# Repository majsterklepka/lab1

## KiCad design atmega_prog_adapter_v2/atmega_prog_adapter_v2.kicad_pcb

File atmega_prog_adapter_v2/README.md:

# ATmega adapter
electronics workshop

Hi!

Now here I present a project of ATmega programmer adapter. For what is them? For You! Schematic is very simple, just one ZIF socket, one Kanda socket and a few discrete elements. Project was made with use of KiCad, and graphics are prepare with use of Inkscape. Below I present a Schematic Sheet:

This adapter is used for flashing following devices:

- ATmega48A
- ATmega48PA
- ATmega88A
- ATmega88PA
- ATmega168A
- ATmega168PA
- ATmega328
- ATmega328P

Of course this adapter needs to work a programmer, for example: USBasp or ArduinoISP. Below is shown 3D view of PCB Layout(without showing elements):

and here, is shown a 2d view of PCB Layout:

These all programmers, their projects are published in my repository [here](https://github.com/majsterklepka/avr-programmers.git "MajsterKlepka AVR-PROGRAMMERS Repo")

Have a fun and do not wake up the neighbors during night fun, because this occupation is very addictive and exciting! Feel free and share this project with friends!

_MSc. Paweł Sobótka (SQ7EQE)_

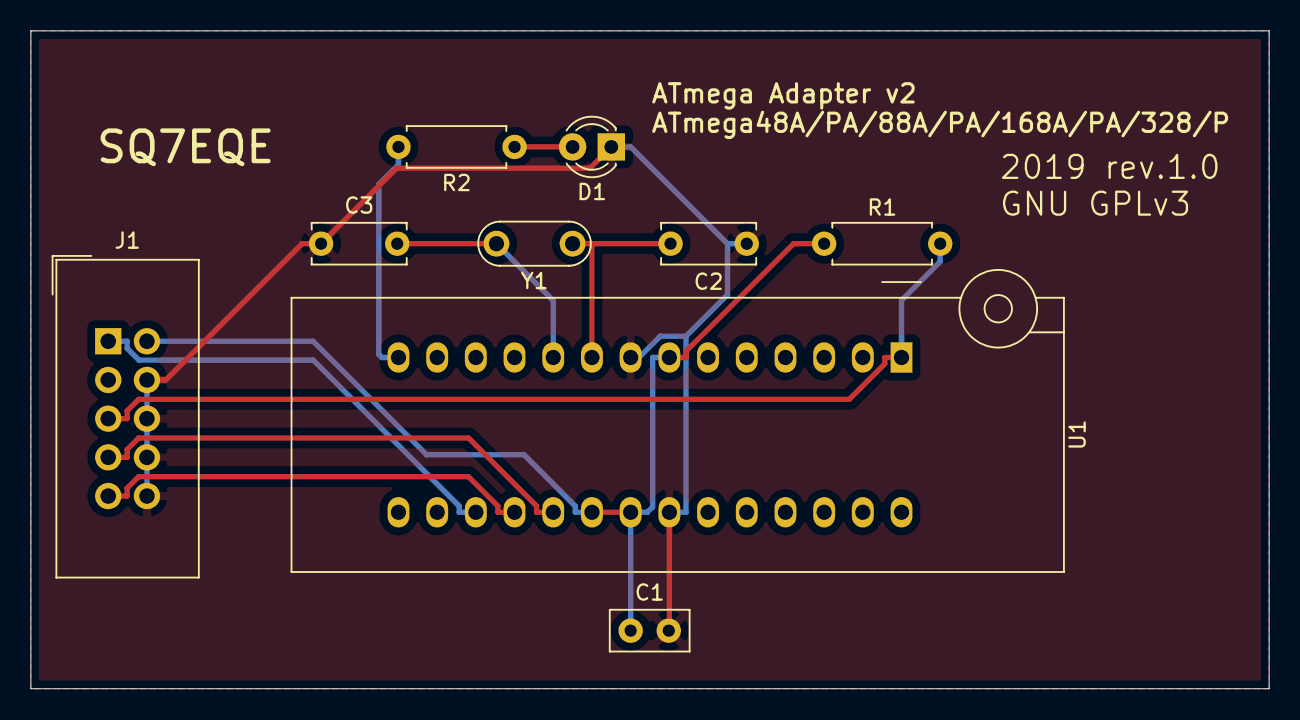
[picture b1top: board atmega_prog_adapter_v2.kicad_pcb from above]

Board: 2 copper layers, 81.3 x 43.2 mm, 9 parts (0 on the bottom side), 10 nets.

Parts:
C1: 0.1u; C_Disc_D5.0mm_W2.5mm_P2.50mm
C2, C3: 22p; C_Disc_D6.0mm_W2.5mm_P5.00mm
D1: YELLOW; LED_D3.0mm
J1: AVR-ISP-10; IDC-Header_2x05_P2.54mm_Vertical
R1: 10k; R_Axial_DIN0207_L6.3mm_D2.5mm_P7.62mm_Horizontal
R2: 470; R_Axial_DIN0207_L6.3mm_D2.5mm_P7.62mm_Horizontal
U1: ATmega48A/PA/88A/PA/168A/PA/328/P; DIP_Socket-28_W6.9_W7.62_W10.16_W12.7_W13.5_3M_228-4817-00-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
Y1: XTAL; Resonator-2Pin_W7.0mm_H2.5mm

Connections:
/MISO: J1.9, U1.18
/MOSI: J1.1, U1.17
/RESET: J1.5, R1.2, U1.1
/SCK: J1.7, U1.19
/XTAL1: C2.2, U1.9, Y1.1
/XTAL2: C3.2, U1.10, Y1.2
GND: C1.2, C2.1, C3.1, D1.1, J1.4, J1.6, J1.8, J1.10, U1.8, U1.22
unnamed: C1.1, J1.2, R1.1, U1.7, U1.20, U1.21
unnamed: D1.2, R2.1
unnamed: R2.2, U1.14

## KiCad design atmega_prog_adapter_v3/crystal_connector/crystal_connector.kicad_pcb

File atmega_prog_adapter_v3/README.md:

# ATmega adapter v3
electronics workshop

Hi, My Dear Friends! 

Here we have the next version of my ATmega adapter project. This project has excluded from main circuit quartz crystal with capacitors, which is a separate module, a sub-project. Of course, this project was created using KiCad and, like the others, is licensed under Free License (GNU GPLv3). The root directory contains Gerber files, as does the sub-project directory. Today I do not place any graphics, all the necessary information is in the documentation.

Feel free and share this project with your friends!

_MSc. Paweł Sobótka (SQ7EQE)_

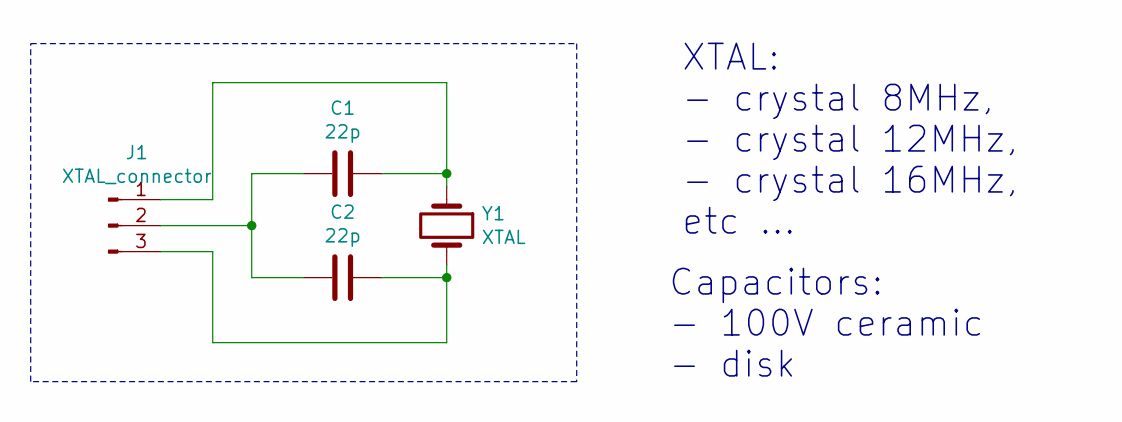
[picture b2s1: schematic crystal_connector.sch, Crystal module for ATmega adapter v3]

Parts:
C1, C2: 22p; C_Disc_D4.3mm_W1.9mm_P5.00mm
J1: XTAL_connector; PinHeader_1x03_P2.54mm_Horizontal
Y1: XTAL; Crystal_HC50_Vertical

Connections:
unnamed: C1.1, J1.1, Y1.1
unnamed: C1.2, C2.2, J1.2
unnamed: C2.1, J1.3, Y1.2

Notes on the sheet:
XTAL: - crystal 8MHz, - crystal 12MHz, - crystal 16MHz, etc ...
Capacitors: - 100V ceramic - disk

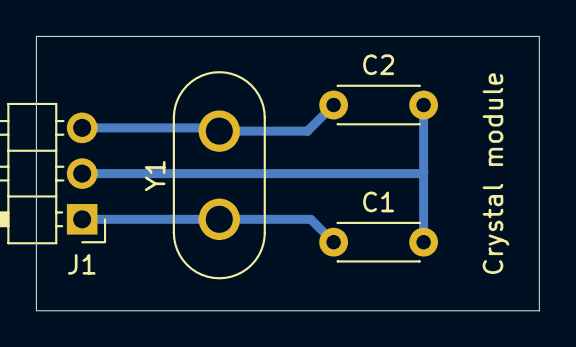
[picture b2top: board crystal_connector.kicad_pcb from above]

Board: 2 copper layers, 27.9 x 15.2 mm, 4 parts (0 on the bottom side), 3 nets.

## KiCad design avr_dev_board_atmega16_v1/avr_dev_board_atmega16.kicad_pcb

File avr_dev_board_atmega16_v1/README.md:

# AVR Atmega16 Dev Board v1
electronics workshop

Hi! Here I have a proposal for you! A Development AVR Board with Atmega16A microcontrollers. This version haven't built-in linear voltage regulator, here you see a 3D PCB layout view:

Schematic sheet is present below and of course, as KiCad project into this folder:

And, as you see, PCB layout project:

Of course, you can look inside drawings/ folder, you see there a PDF documents.

Have a fun with that project!

_MSc. Paweł Sobótka (SQ7EQE)_

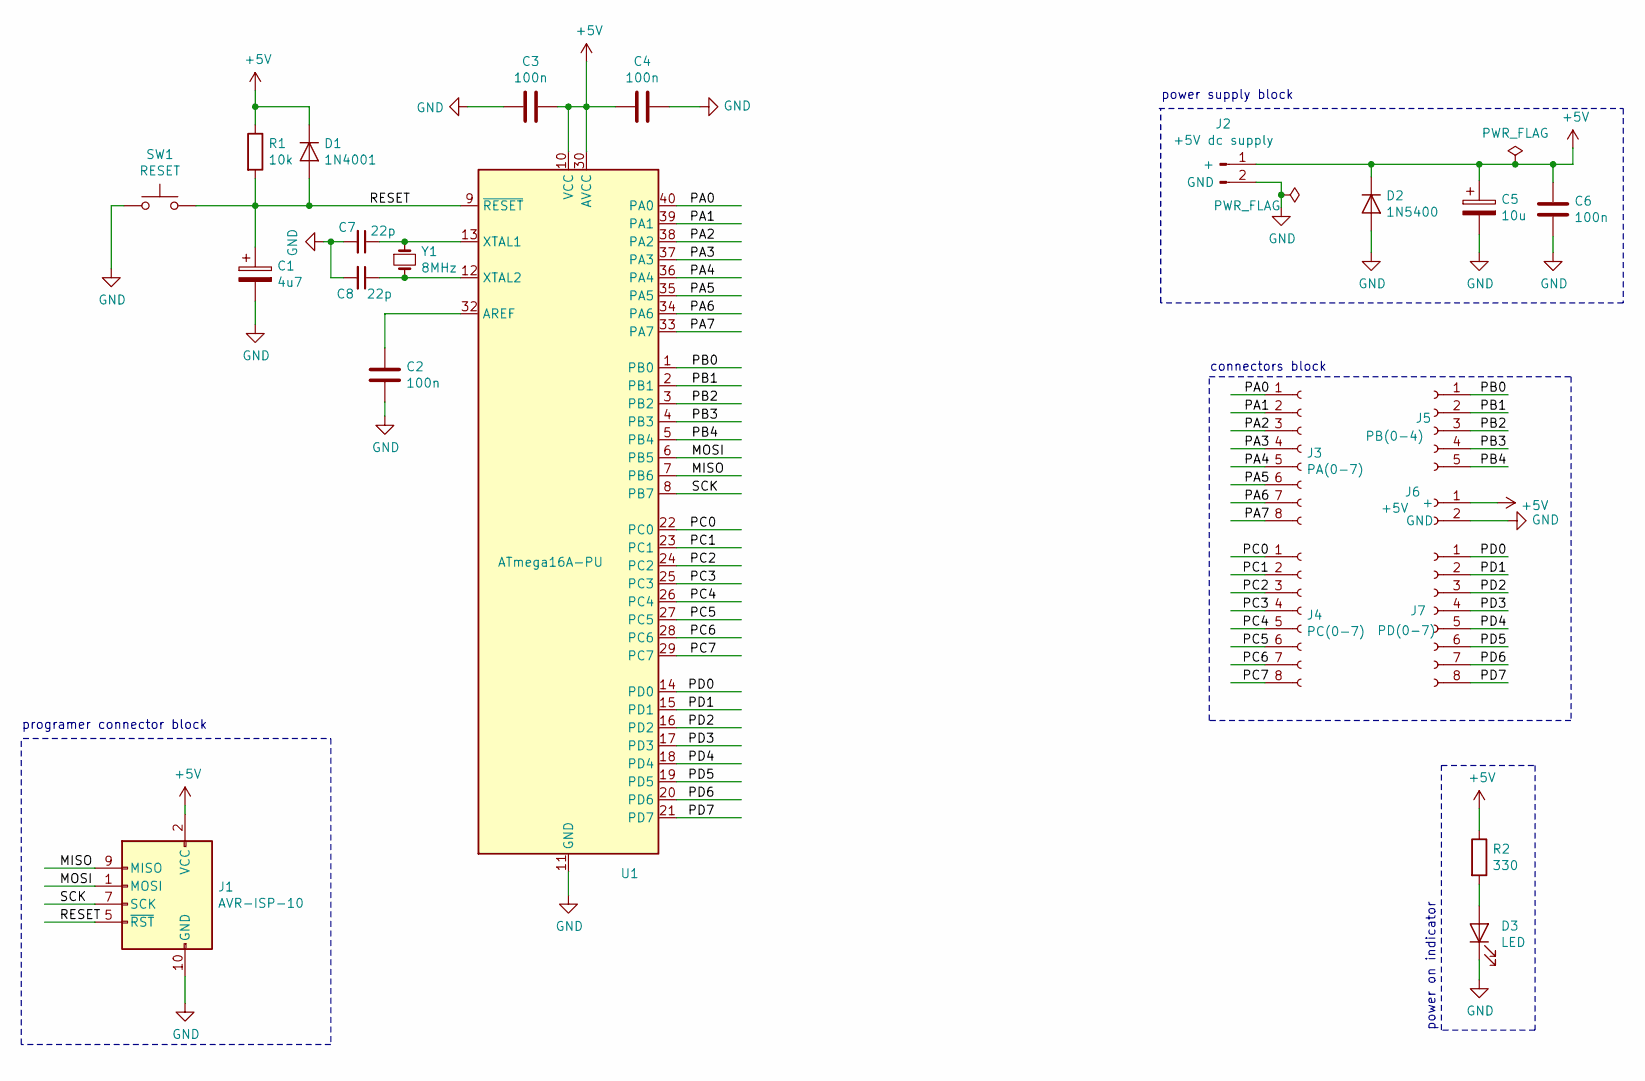
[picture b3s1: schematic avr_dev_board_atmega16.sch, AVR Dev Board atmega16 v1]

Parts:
C1: 4u7; CP_Radial_D5.0mm_P2.50mm
C2, C3, C4, C6: 100n; C_Disc_D4.3mm_W1.9mm_P5.00mm
C5: 10u; CP_Radial_D6.3mm_P2.50mm
C7, C8: 22p; C_Disc_D4.7mm_W2.5mm_P5.00mm
D1: 1N4001; D_DO-41_SOD81_P10.16mm_Horizontal
D2: 1N5400; D_DO-201AD_P15.24mm_Horizontal
D3: LED; LED_D3.0mm
J1: AVR-ISP-10; IDC-Header_2x05_P2.54mm_Vertical
J2: +5V dc supply; PinHeader_1x02_P2.54mm_Vertical_PWR
J3: PA(0-7); PinSocket_1x08_P2.54mm_Vertical_PA
J4: PC(0-7); PinSocket_1x08_P2.54mm_Vertical_PC
J5: PB(0-4); PinSocket_1x05_P2.54mm_Vertical_PB
J6: +5V; PinSocket_1x02_P2.54mm_Vertical_PWR
J7: PD(0-7); PinSocket_1x08_P2.54mm_Vertical_PD
R1: 10k; R_Axial_DIN0309_L9.0mm_D3.2mm_P2.54mm_Vertical
R2: 330; R_Axial_DIN0309_L9.0mm_D3.2mm_P2.54mm_Vertical
SW1: RESET; SW_PUSH_6mm_H5mm
U1: ATmega16A-PU; DIP-40_W15.24mm
Y1: 8MHz; Resonator-2Pin_W6.0mm_H3.0mm

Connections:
+5V: C3.1, C4.2, C5.1, C6.1, D1.1 (K), D2.1 (K), J1.2 (VCC), J2.1 (+), J6.1 (+), R1.1, R2.1, U1.10 (VCC), U1.30 (AVCC)
/MISO: J1.9 (MISO), U1.7 (PB6)
/MOSI: J1.1 (MOSI), U1.6 (PB5)
/PA0: J3.1, U1.40 (PA0)
/PA1: J3.2, U1.39 (PA1)
/PA2: J3.3, U1.38 (PA2)
/PA3: J3.4, U1.37 (PA3)
/PA4: J3.5, U1.36 (PA4)
/PA5: J3.6, U1.35 (PA5)
/PA6: J3.7, U1.34 (PA6)
/PA7: J3.8, U1.33 (PA7)
/PB0: J5.1, U1.1 (PB0)
/PB1: J5.2, U1.2 (PB1)
/PB2: J5.3, U1.3 (PB2)
/PB3: J5.4, U1.4 (PB3)
/PB4: J5.5, U1.5 (PB4)
/PC0: J4.1, U1.22 (PC0)
/PC1: J4.2, U1.23 (PC1)
/PC2: J4.3, U1.24 (PC2)
/PC3: J4.4, U1.25 (PC3)
/PC4: J4.5, U1.26 (PC4)
/PC5: J4.6, U1.27 (PC5)
/PC6: J4.7, U1.28 (PC6)
/PC7: J4.8, U1.29 (PC7)
/PD0: J7.1, U1.14 (PD0)
/PD1: J7.2, U1.15 (PD1)
/PD2: J7.3, U1.16 (PD2)
/PD3: J7.4, U1.17 (PD3)
/PD4: J7.5, U1.18 (PD4)
/PD5: J7.6, U1.19 (PD5)
/PD6: J7.7, U1.20 (PD6)
/PD7: J7.8, U1.21 (PD7)
/RESET: C1.1, D1.2 (A), J1.5 (~RST), R1.2, SW1.2, U1.9 (~RESET)
/SCK: J1.7 (SCK), U1.8 (PB7)
GND: C1.2, C2.2, C3.2, C4.1, C5.2, C6.2, C7.2, C8.2, D2.2 (A), D3.1 (K), J1.4 (GND), J1.6 (GND), J1.8 (GND), J1.10 (GND), J2.2 (GND), J6.2 (GND), SW1.1, U1.11 (GND), U1.31 (GND)
unnamed: C2.1, U1.32 (AREF)
unnamed: C7.1, U1.13 (XTAL1), Y1.1
unnamed: C8.1, U1.12 (XTAL2), Y1.2
unnamed: D3.2 (A), R2.2

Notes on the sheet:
power supply block
connectors block
programer connector block
power on indicator

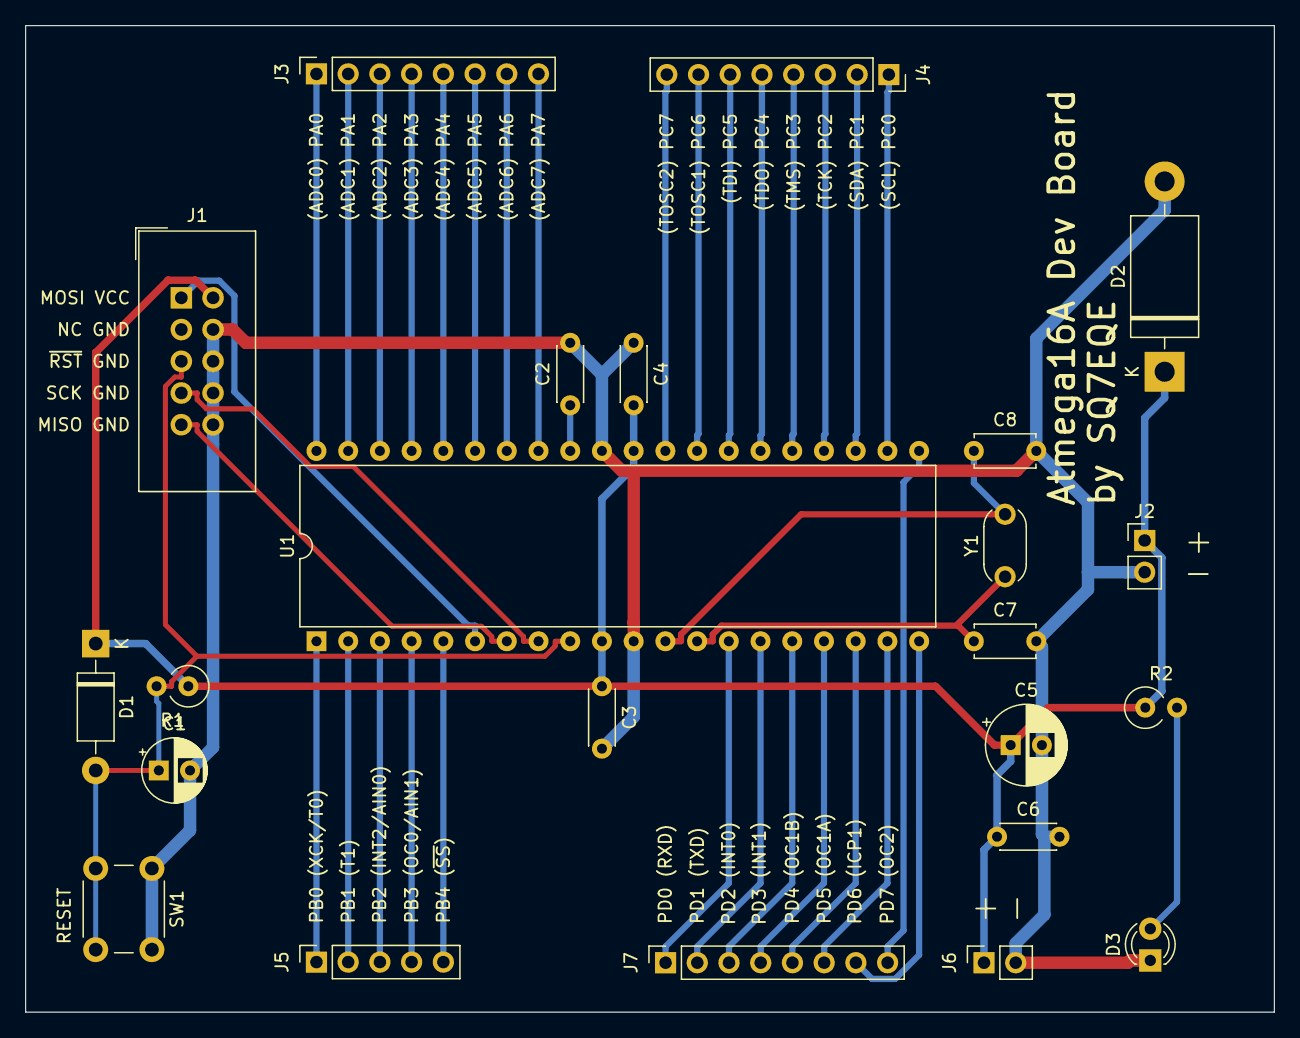
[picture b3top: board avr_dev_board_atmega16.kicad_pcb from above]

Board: 2 copper layers, 100.0 x 79.0 mm, 23 parts (0 on the bottom side), 39 nets.

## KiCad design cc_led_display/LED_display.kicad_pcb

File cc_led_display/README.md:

# Experimental CC LED Display
electronics workshop

Now, I present a simple, no! The simplest project, one difficulty is that this project requires double side PCB. You can use them for Arduino Projects, AVR Projects(for example with my Dev Board) and for what you only wish! Here is a schematic diagram:

Here You have a view of PCB in 3D, generated with Kicad 3DView:

What you need to make this project? Here is a list

- 8 x 1k resistor 0.125W
- 1 x OPD-S5621G-BW LED display with common cathode
- 1 x PCB
- solder, soldering iron, flux, side cutters, tweezers ...

I will be forgotten! I make a PCB project too! Here you have one:

Have fun! Feel free and share this project with friends! The project has two licenses: GNU GPLv3 and GNU FDL-1.3. You can use it as you wish, but please, remember about The Author!

_MSc. Paweł Sobótka (SQ7EQE)_

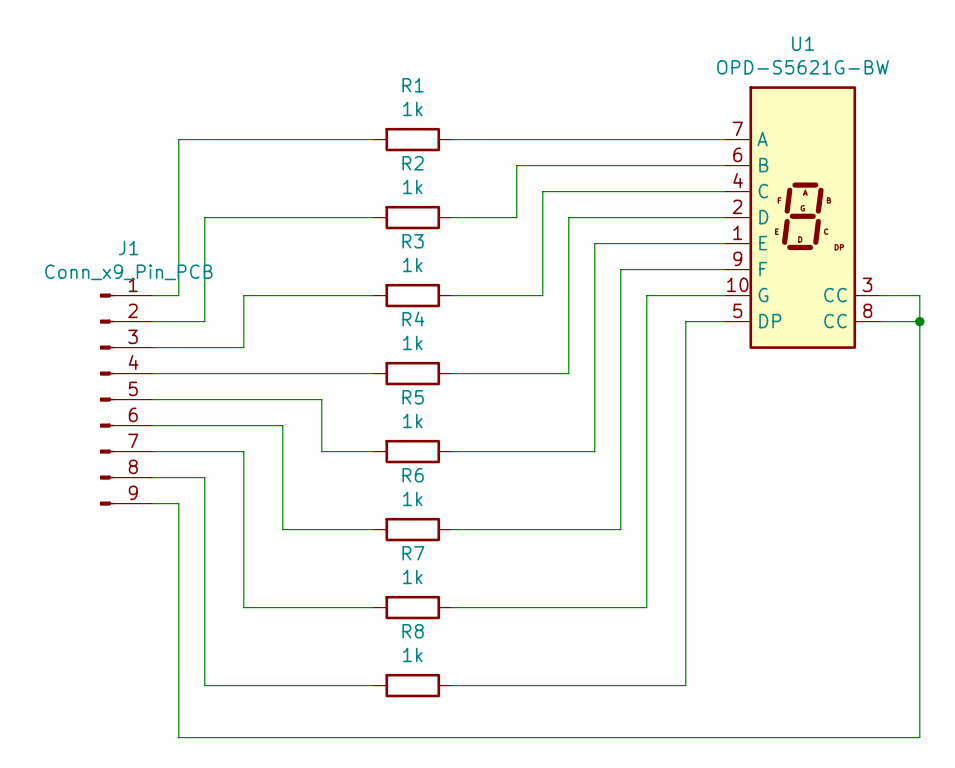
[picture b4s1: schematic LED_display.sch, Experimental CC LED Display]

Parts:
J1: Conn_x9_Pin_PCB; con_pingold_9_P2.54
R1, R2, R3, R4, R5, R6, R7, R8: 1k; R_Axial_DIN0204_L3.6mm_D1.6mm_P7.62mm_Horizontal
U1: OPD-S5621G-BW; led_0.56

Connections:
unnamed: J1.1, R1.2
unnamed: J1.2, R2.2
unnamed: J1.3, R3.2
unnamed: J1.4, R4.2
unnamed: J1.5, R5.2
unnamed: J1.6, R6.2
unnamed: J1.7, R7.2
unnamed: J1.8, R8.2
unnamed: J1.9, U1.3 (CC), U1.8 (CC)
unnamed: R1.1, U1.7 (A)
unnamed: R2.1, U1.6 (B)
unnamed: R3.1, U1.4 (C)
unnamed: R4.1, U1.2 (D)
unnamed: R5.1, U1.1 (E)
unnamed: R6.1, U1.9 (F)
unnamed: R7.1, U1.10 (G)
unnamed: R8.1, U1.5 (DP)

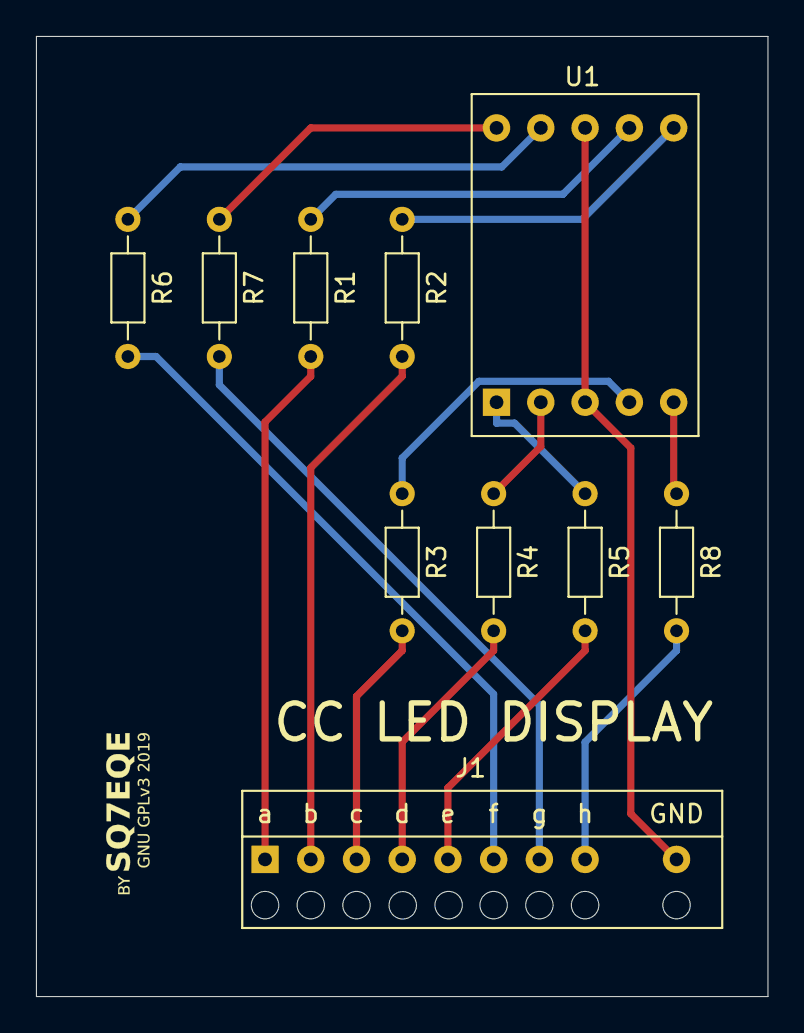
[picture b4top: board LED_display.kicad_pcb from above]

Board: 2 copper layers, 40.6 x 53.3 mm, 10 parts (0 on the bottom side), 17 nets.

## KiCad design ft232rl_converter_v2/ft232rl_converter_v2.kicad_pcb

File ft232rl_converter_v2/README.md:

# FT232RL USB-TTL-UART converter ver. 2.0

Hi, My Dear Friends!

Today, I have to present for You New Project. This is a simple use of the Manufacturer Application Note of FT232RL chip. Here you have a 3D View of PCB layout:

At the root tree of the project folder, you can find a file named BOM with various extensions. This is a list used in the project materials. Of course, I remember about ship to you a schematic diagram, here we have one:

Especially for You, I have design the PCB layout, here you have one:

In the folder named plot/ I have placed a generated Gerber files for the project.

And like usual, this project is licensed under GNU GPLv3 license and FDL-1.3 license. Feel free! Share this project with friends and don't forget about author ye the way!

See You Later & with my pleasure for You!

_MSc. Paweł Sobótka (SQ7EQE)_

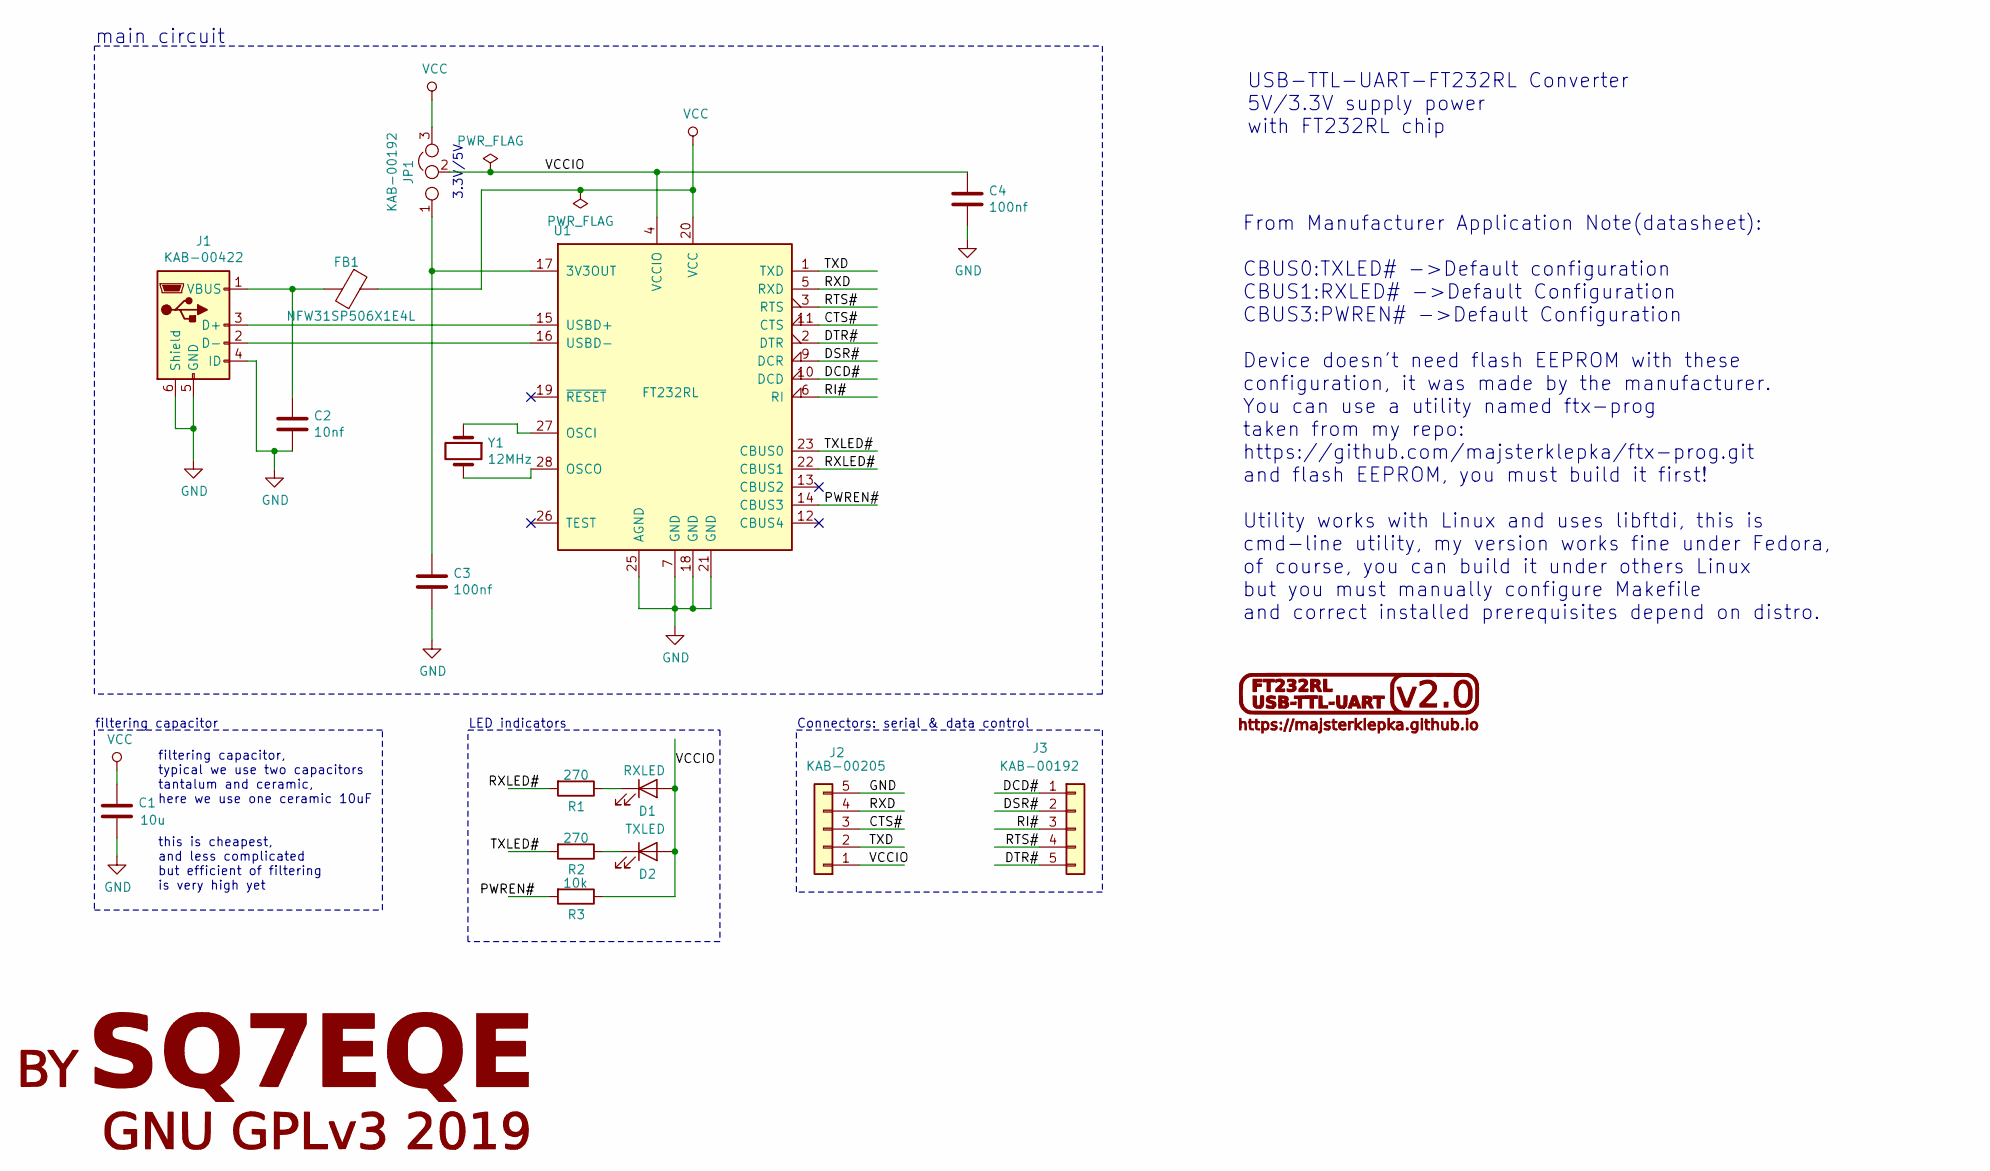
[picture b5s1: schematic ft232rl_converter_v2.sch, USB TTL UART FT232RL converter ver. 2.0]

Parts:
C1: 10u; C_1206_3216Metric_Pad1.42x1.75mm_HandSolder; Part C1206C106K9RACTU
C2: 10nf; C_1206_3216Metric_Pad1.42x1.75mm_HandSolder; Part KC10nF_1206
C3, C4: 100nf; C_1206_3216Metric_Pad1.42x1.75mm_HandSolder; Part KC100nF_1206
D1: RXLED; D_1206_3216Metric_Pad1.42x1.75mm_HandSolder; Part LED-01458
D2: TXLED; D_1206_3216Metric_Pad1.42x1.75mm_HandSolder; Part LED-01458
FB1: NFW31SP506X1E4L; R_1206_3216Metric_Pad1.42x1.75mm_HandSolder; Part NFW31SP506X1E4L
J1: KAB-00422; USB_Micro-B_Molex_47346-0001; Part KAB-00422
J2: KAB-00205; PinHeader_1x05_P2.54mm_Horizontal; Part KAB-00205
J3: KAB-00192; PinHeader_1x05_P2.54mm_Vertical; Part KAB-00192
JP1: KAB-00192; PinHeader_1x03_P2.54mm_Vertical; Part KAB-00192
R1, R2: 270; R_0805_2012Metric_Pad1.15x1.40mm_HandSolder; Part R270 805
R3: 10k; R_1206_3216Metric_Pad1.42x1.75mm_HandSolder; Part R10K_1206
U1: FT232RL; SSOP-28_5.3x10.2mm_P0.65mm; Part FT232RL
Y1: 12MHz; Crystal_HC49-U_Vertical; Part Q12MHZ_N

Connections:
/CTS#: J2.3, U1.11 (CTS)
/DCD#: J3.1, U1.10 (DCD)
/DSR#: J3.2, U1.9 (DCR)
/DTR#: J3.5, U1.2 (DTR)
/PWREN#: R3.2, U1.14 (CBUS3)
/RI#: J3.3, U1.6 (RI)
/RTS#: J3.4, U1.3 (RTS)
/RXD: J2.4, U1.5 (RXD)
/RXLED#: R1.2, U1.22 (CBUS1)
/TXD: J2.2, U1.1 (TXD)
/TXLED#: R2.2, U1.23 (CBUS0)
/VCCIO: C4.1, D1.2 (A), D2.2 (A), J2.1, JP1.2, R3.1, U1.4 (VCCIO)
GND: C1.2, C2.2, C3.2, C4.2, J1.4 (ID), J1.5 (GND), J1.6 (Shield), J2.5, U1.7 (GND), U1.18 (GND), U1.21 (GND), U1.25 (AGND)
unnamed: C2.1, FB1.2, J1.1 (VBUS)
unnamed: C3.1, JP1.1, U1.17 (3V3OUT)
unnamed: D1.1 (K), R1.1
unnamed: D2.1 (K), R2.1
unnamed: J1.2 (D-), U1.16 (USBD-)
unnamed: J1.3 (D+), U1.15 (USBD+)
unnamed: U1.27 (OSCI), Y1.1
unnamed: U1.28 (OSCO), Y1.2
VCC: C1.1, FB1.1, JP1.3, U1.20 (VCC)

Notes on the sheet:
Connectors: serial & data control
filtering capacitor
USB-TTL-UART-FT232RL Converter 5V/3.3V supply power with FT232RL chip
main circuit
From Manufacturer Application Note(datasheet): CBUS0:TXLED# ->Default configuration CBUS1:RXLED# ->Default Configuration CBUS3:PWREN# ->Default Configuration Device doesn't need flash EEPROM with these configuration, it was made by the manufacturer. You can use a utility named ftx-prog taken from m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
LED indicators
3.3V/5V
filtering capacitor, typical we use two capacitors tantalum and ceramic, here we use one ceramic 10uF
this is cheapest, and less complicated but efficient of filtering is very high yet

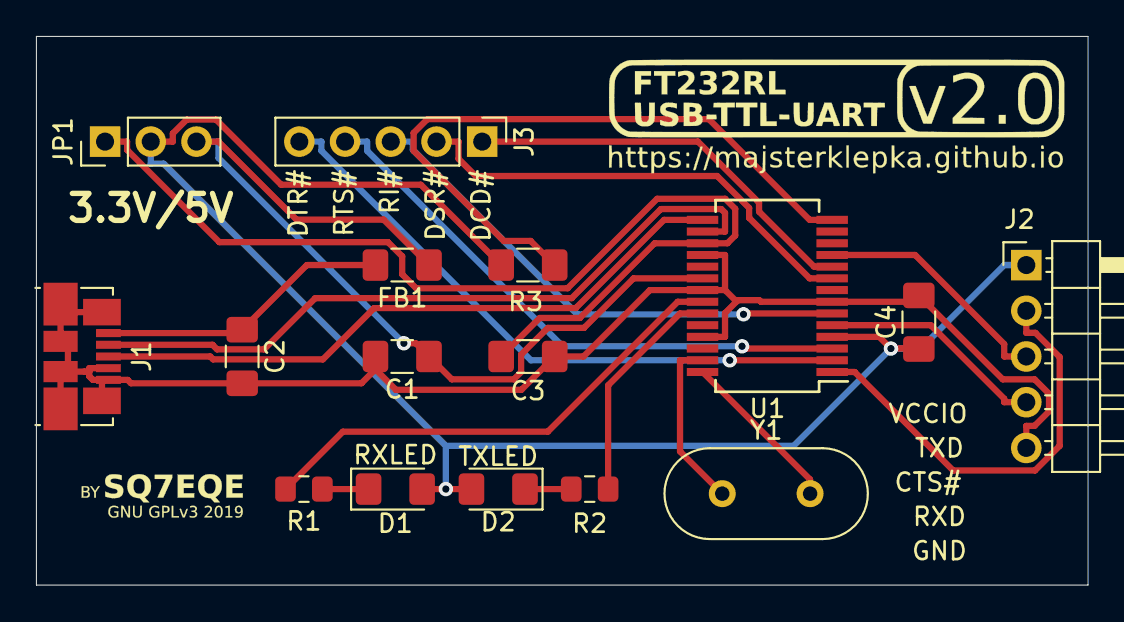
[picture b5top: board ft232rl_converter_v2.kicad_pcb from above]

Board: 2 copper layers, 58.4 x 30.5 mm, 16 parts (0 on the bottom side), 22 nets.

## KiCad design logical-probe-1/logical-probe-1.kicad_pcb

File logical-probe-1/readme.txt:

Function 	Red LED		Yellow LED	Green LED
------------------------------------------------------------
On 		OFF		OFF		ON
------------------------------------------------------------
Off		ON		OFF		OFF
------------------------------------------------------------
Oscillating	ON		ON		ON
------------------------------------------------------------
Floating	OFF		ON		OFF
------------------------------------------------------------

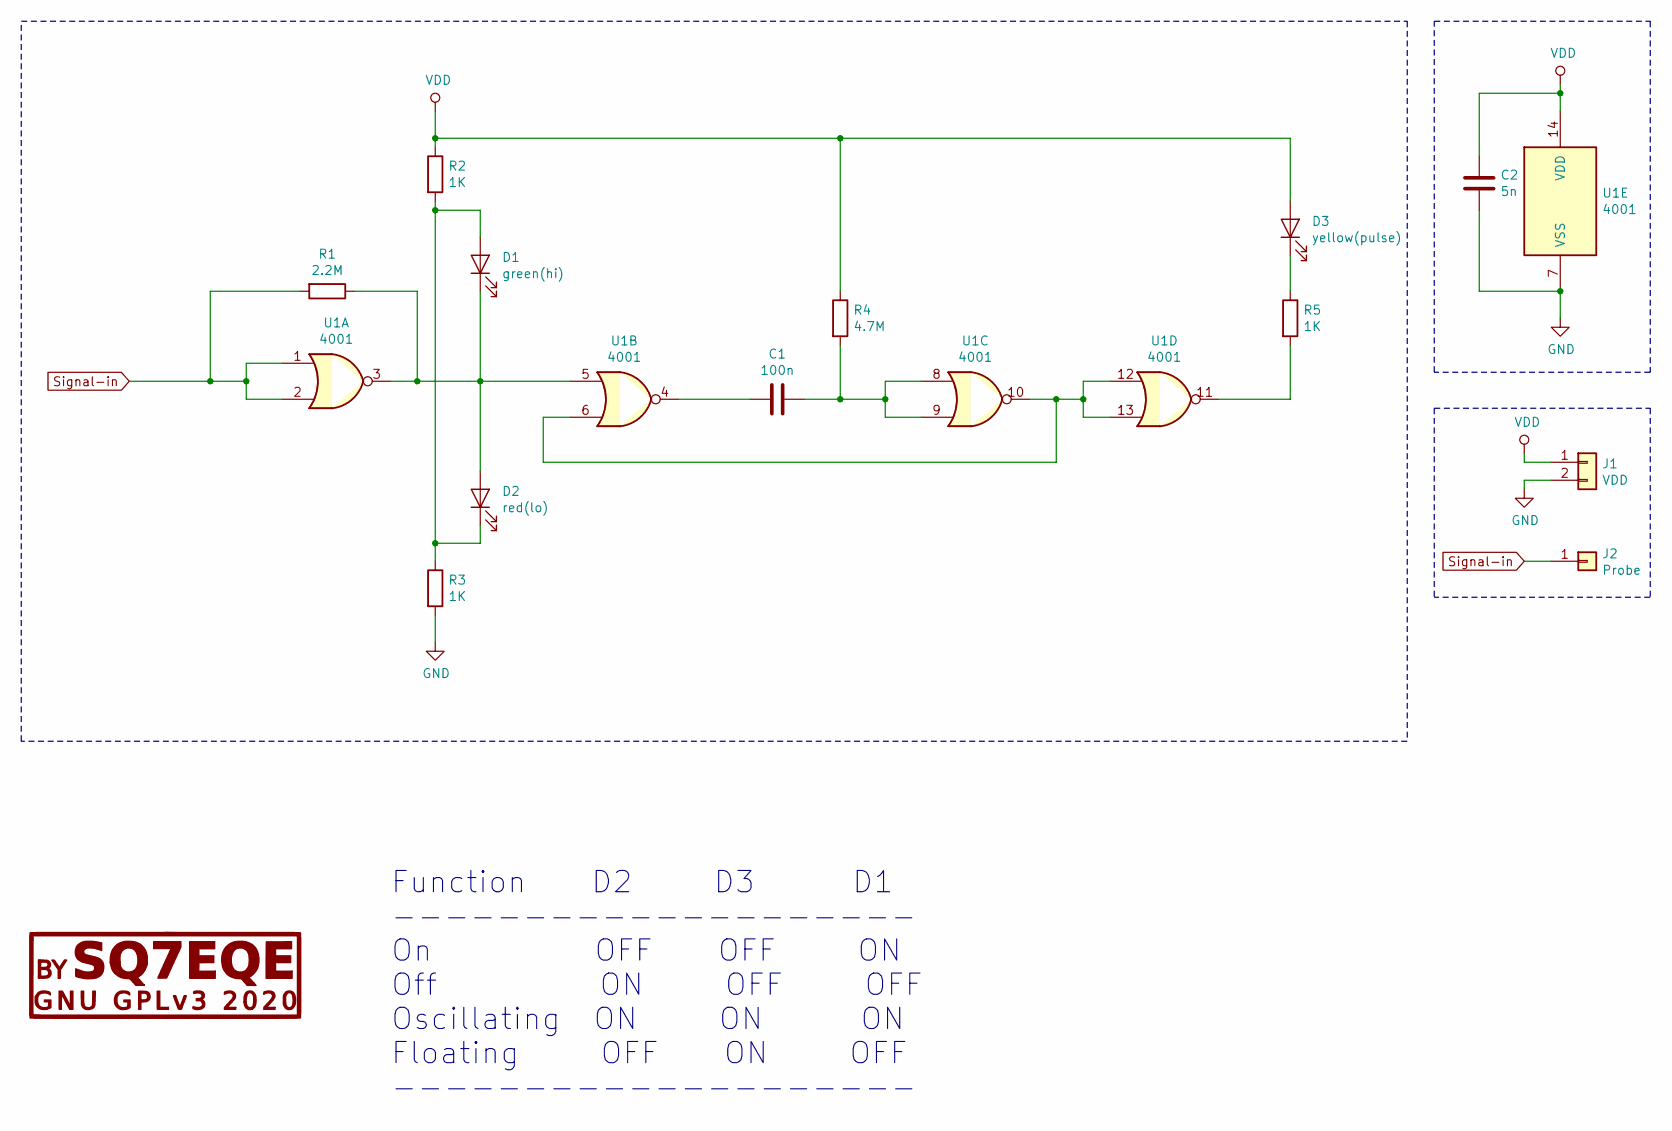
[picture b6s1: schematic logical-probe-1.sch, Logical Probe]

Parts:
C1: 100n; C_Disc_D5.0mm_W2.5mm_P2.50mm
C2: 5n; C_Disc_D5.0mm_W2.5mm_P2.50mm
D1: green(hi); LED_D3.0mm
D2: red(lo); LED_D3.0mm
D3: yellow(pulse); LED_D3.0mm
J1: VDD; VDD-battery
J2: Probe; probe_1mm
R1: 2.2M; R_Axial_DIN0207_L6.3mm_D2.5mm_P7.62mm_Horizontal
R2, R3, R5: 1K; R_Axial_DIN0207_L6.3mm_D2.5mm_P7.62mm_Horizontal
R4: 4.7M; R_Axial_DIN0207_L6.3mm_D2.5mm_P7.62mm_Horizontal
U1: 4001; DIP-14_W7.62mm

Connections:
GND: C2.2, J1.2, R3.2, U1.7 (VSS)
unnamed: C1.1, R4.2, U1.8, U1.9
unnamed: C1.2, U1.4
unnamed: D1.1 (K), D2.2 (A), R1.1, U1.3, U1.5
unnamed: D1.2 (A), D2.1 (K), R2.2, R3.1
unnamed: D3.1 (K), R5.1
unnamed: R5.2, U1.11
unnamed: U1.6, U1.10, U1.12, U1.13
Signal-in: J2.1, R1.2, U1.1, U1.2
VDD: C2.1, D3.2 (A), J1.1, R2.1, R4.1, U1.14 (VDD)

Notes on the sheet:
Function D2 D3 D1 -------------------- On OFF OFF ON Off ON OFF OFF Oscillating ON ON ON Floating OFF ON OFF --------------------

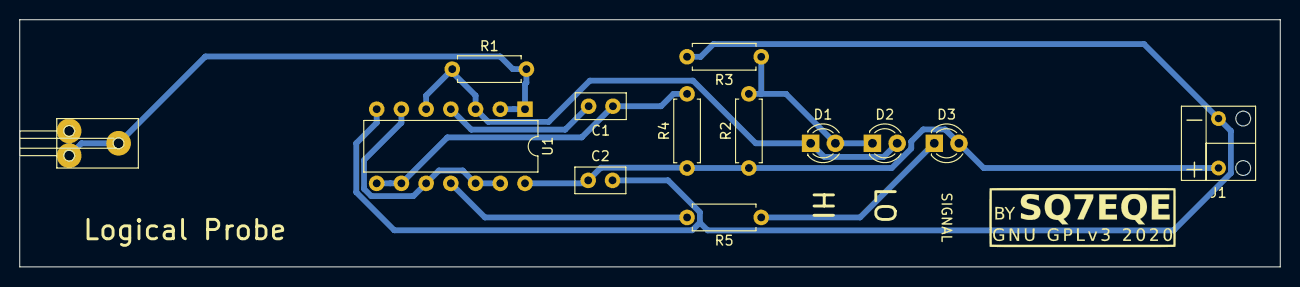
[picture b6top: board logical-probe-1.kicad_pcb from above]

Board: 2 copper layers, 129.5 x 25.4 mm, 13 parts (0 on the bottom side), 10 nets.

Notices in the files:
avr_dev_board_atmega16_v1/avr_dev_board_atmega16.kicad_pcb:
GNU GPL v3 or later
